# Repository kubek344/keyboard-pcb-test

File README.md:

# keyboard-pcb-test
 Learning how to make my own keyboard PCB

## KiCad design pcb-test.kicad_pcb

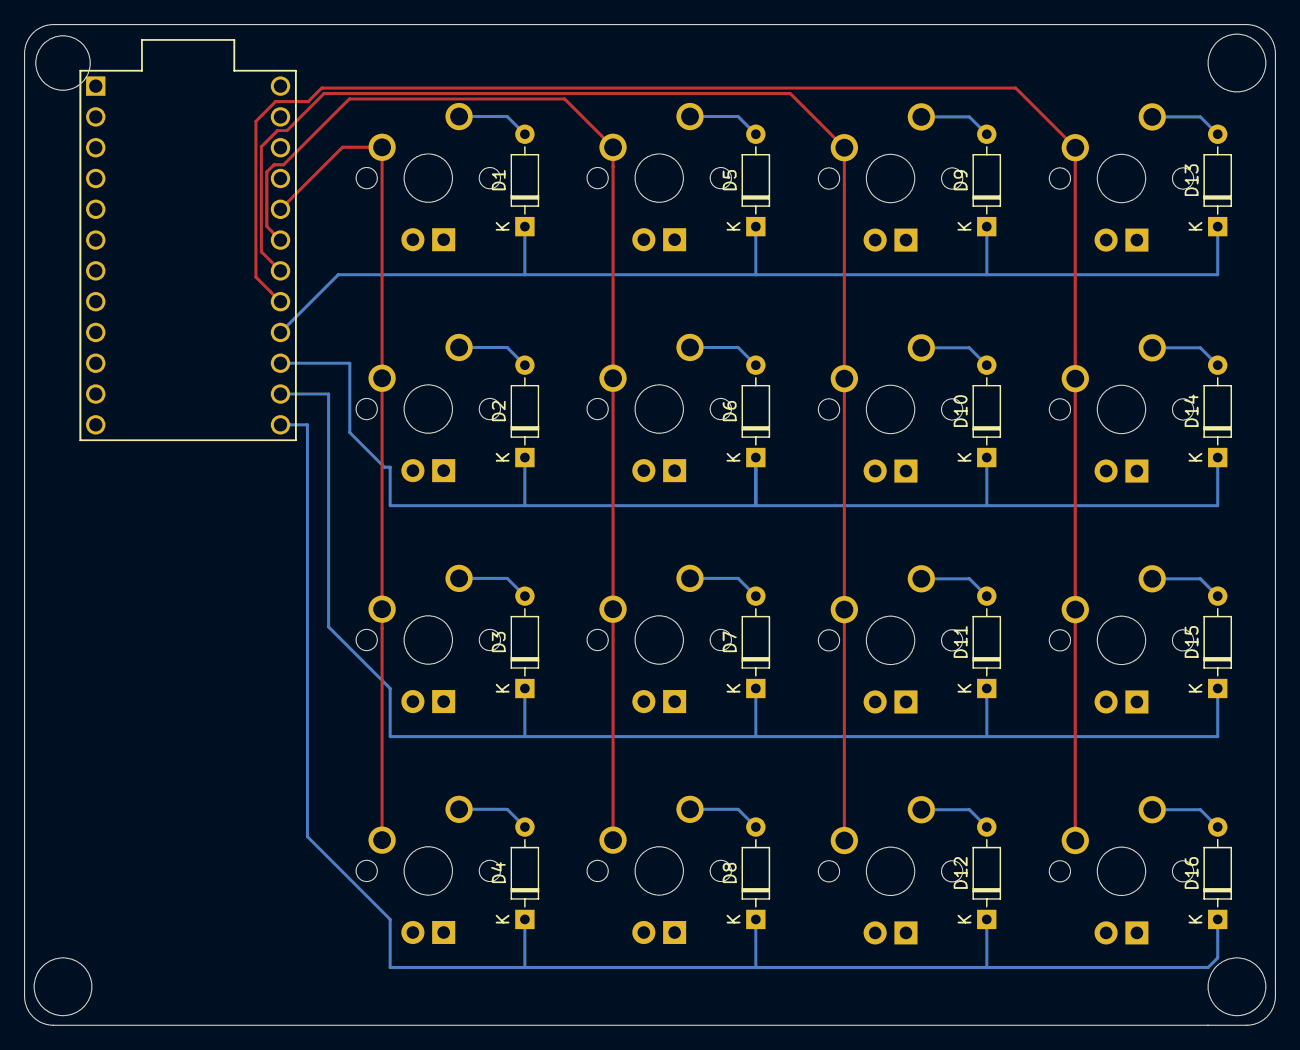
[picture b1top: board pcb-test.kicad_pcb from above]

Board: 2 copper layers, 103.2 x 82.5 mm, 33 parts (0 on the bottom side), 24 nets.

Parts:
D1, D2, D3, D4, D5, D6, D7, D8, D9, D10, D11, D12, D13, D14, D15, D16: D_Small; D_DO-35_SOD27_P7.62mm_Horizontal
MX1, MX2, MX3, MX4, MX5, MX6, MX7, MX8, MX9, MX10, MX11, MX12, MX13, MX14, MX15, MX16: MX-NoLED; MXOnly-1U
U1: ProMicro

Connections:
unnamed: D1.2, MX1.2
unnamed: D2.2, MX2.2
unnamed: D3.2, MX3.2
unnamed: D4.2, MX4.2
unnamed: D5.2, MX5.2
unnamed: D6.2, MX6.2
unnamed: D7.2, MX7.2
unnamed: D8.2, MX8.2
unnamed: D9.2, MX9.2
unnamed: D10.2, MX10.2
unnamed: D11.2, MX11.2
unnamed: D12.2, MX12.2
unnamed: D13.2, MX13.2
unnamed: D14.2, MX14.2
unnamed: D15.2, MX15.2
unnamed: D16.2, MX16.2
col0: MX1.1, MX2.1, MX3.1, MX4.1, U1.20
col1: MX5.1, MX6.1, MX7.1, MX8.1, U1.19
col2: MX9.1, MX10.1, MX11.1, MX12.1, U1.18
col3: MX13.1, MX14.1, MX15.1, MX16.1, U1.17
row0: D1.1, D5.1, D9.1, D13.1, U1.16
row1: D2.1, D6.1, D10.1, D14.1, U1.15
row2: D3.1, D7.1, D11.1, D15.1, U1.14
row3: D4.1, D8.1, D12.1, D16.1, U1.13

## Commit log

2021-04-01 Initialize project
2021-04-01 Add submodules
2021-04-01 Add footprint libraries
2021-04-01 Added MCU schematic
2021-04-01 Bigger changes
    Decided to stop relying on tutorial and started to do things on my own, used arduino pro micro instead of wiring atmega on my own. Sketch is now finished.
2021-04-02 Finished PCB design
2021-04-02 Small adjustments
2021-04-02 Changed the placement of diodes
